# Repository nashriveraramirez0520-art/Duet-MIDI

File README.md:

# Duet-MIDI

I wanted to make something I could use to play both melodies and drums without needing two separate controllers. That is where Duet-MIDI started: eight touch pads, two modes, and a few extra controls to make it more fun to play.

This is my project for **Hack Club Half Life, Week 3: Music**. The schematic and PCB layout are finished, the Gerbers have been exported and checked, and the first enclosure version is modeled in Onshape. I have also prepared a first CircuitPython firmware version. I still need to print it, build the board, and test the firmware, so the pictures below are from KiCad, not a working prototype.

## What I want it to do

In melody mode, the eight pads will play notes from a scale, with buttons to move up or down an octave. In drum mode, the same pads will trigger different drum sounds. I added a mode button so I can switch between them instead of having to choose just one idea.

There is also a slider, a rotary encoder with a push switch, and a function button. Their exact MIDI assignments are still something I need to work out in the firmware. Eight RGB LEDs will give feedback for the mode and the pads being played.

It will connect to a computer over USB for both power and MIDI. The sound will come from a software instrument or drum sampler on the computer.

## The board

The PCB is **100 × 91.75 mm**, with two copper layers and four M2 mounting holes. I kept the touch pads in two rows of four, put the slider on the left, and placed the other controls below the pads. The RGB LEDs sit on the back and shine through eight openings near the top.

| Part | What it does |
| --- | --- |
| Waveshare ESP32-S3-Zero | USB connection and main controller |
| 8 capacitive touch pads | Note and drum inputs |
| MCP23008 | Reads the four buttons and the encoder push switch |
| Rotary encoder and 10 kΩ slider | Additional MIDI controls |
| 8 SK6812MINI-E RGB LEDs | Visual feedback |
| 74AHCT125 | Converts the RGB data signal from 3.3 V to 5 V |

## Getting the layout finished

Routing took a lot of small fixes. I had to work around the touch pads, connect the LEDs in the right order, and keep checking the remaining unconnected items as I went. Eventually the routing check reached zero violations and zero unconnected items with schematic parity turned off. That was a really nice point to reach after seeing the list slowly go down.

I then moved the reference text that was outside the board, added the control labels, and checked the exported copper, outline, and drill layers in Gerber Viewer.

[Routing check screenshot](docs/images/routing-drc.png) · [Back view](docs/images/pcb-back-3d.png)

The routing screenshot is from before the final text cleanup. Five DRC checks were disabled in that run; the details and the remaining manufacturing checks are in [pcb/README.md](pcb/README.md). The electrical behavior still needs to be tested on real hardware.

## The enclosure

I wanted a case I could open again, with the touch area accessible and a window underneath to show part of the PCB. V1 has a separate lid, four button extensions, a knob for the encoder, and a grip for the slider. The lid uses the same four M2 mounting positions as the board.

I had to lower the ESP32 mounting height to keep the case even across the top. I also adjusted the small control sockets and checked the slider at the center and both ends. The next step is a real fit test, starting with the small pieces before printing the whole enclosure.

[Enclosure files and assembly notes](cad/README.md) — includes individual STEP and STL parts plus a reference assembly. The bottom window is designed for separate 1 mm acrylic.

## Files

- [KiCad project](pcb/Duet-MIDI.kicad_pro), [schematic](pcb/Duet-MIDI.kicad_sch), and [PCB](pcb/Duet-MIDI.kicad_pcb).
- [Gerber ZIP](pcb/Duet-MIDI-Gerbers.zip) and [individual manufacturing files](pcb/gerbers/).
- [PCB notes and library setup](pcb/README.md).
- [CircuitPython firmware V1](firmware/), [enclosure V1](cad/), and [development journal](JOURNAL.md).
- [BOM draft](BOM.csv), with quantities extracted from the PCB. Exact parts, suppliers and prices are still pending; see [BOM notes](docs/BOM-notes.md).

To open the design, download the repository and open `pcb/Duet-MIDI.kicad_pro` in **KiCad 10**. The custom touch-pad footprint and the Hack Club libraries used by the design are included with project-relative paths.

## Firmware progress

The first CircuitPython version now includes both pad modes, octave buttons, a panic button, slider modulation, encoder volume with push-to-reset, and RGB feedback. Desktop tests cover the note and control logic, but I have not tested USB MIDI or any of the physical controls on the board yet. Touch thresholds, encoder settings, lighting and power use still need checking.

## What is next

The next steps are to finish the parts list, confirm the manufacturing limits, print and fit-test enclosure V1, and test the first firmware version on hardware. After assembly, I will need to test USB MIDI, calibrate the touch pads, and check the buttons, slider, encoder, and lighting together.

One thing still to confirm before ordering is the **0.20 mm copper clearance around the internal LED cutouts**. The LED brightness and USB power budget also need to be handled before running the assembled board.

## Editable CAD Source(Onshape)
https://cad.onshape.com/documents/5af46204eeb29ad0fa03019d/w/52b0aef6fb09ac80a2bff0bc/e/92c0bc1531caa20fbf243b4c?renderMode=0&uiState=6ade9d325837a28337909538

## References

I started from [Kai Pereira's MIDI Keypad guide](https://github.com/KaiPereira/MIDI-Keypad) and developed this layout around the two-mode idea and the extra controls. The Waveshare symbol and footprint come from [Hackclub KiCad Libraries](https://github.com/KaiPereira/Hackclub-KiCad-Libraries); see [the attribution notes](pcb/libraries/README.md).

Project by **Nash Andrés Rivera Ramírez**.

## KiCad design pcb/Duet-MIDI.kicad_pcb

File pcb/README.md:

# PCB files

The schematic, routed PCB, project rules, custom libraries, and manufacturing exports are here. Open `Duet-MIDI.kicad_pro` in KiCad 10 with the folder structure intact.

## Libraries

`Duet.pretty` contains the eight-pad touch footprint. The project-local `fp-lib-table` also registers `libraries/Hackclub.pretty` under its original name, **Hackclub Footprints**. `sym-lib-table` registers the supplied **Hackclub Symbols** library. Standard components use KiCad's installed libraries.

The Waveshare 3D model is optional and is not bundled here. To display it, download the upstream Hackclub KiCad Libraries and set `HACKCLUB_3DMODEL_DIR` to its `3D models` folder. Missing 3D models do not remove the component footprints from the PCB.

## Board and exports

- Board outline: 100 × 91.75 mm; two copper layers; nominal thickness 1.6 mm.
- Four 2.2 mm non-plated mounting holes for M2 hardware.
- Eight routed openings for the reverse-mount LEDs.
- Seven Gerber layers, separate plated/non-plated drill files, and a Gerber job file are in `gerbers/`.
- `Duet-MIDI-Gerbers.zip` contains the manufacturing export reviewed in Gerber Viewer.

The PCB, schematic, project, and custom rule files are the uploaded design files, unchanged. Only the library registration tables were adjusted for portability. The exports are from the earlier fabrication export in the same design session; regenerate them after any further board edits.

## Checks and remaining work

The supplied routing screenshot shows zero DRC violations and zero unconnected items, with schematic parity disabled. Five checks were ignored: missing courtyard, track endpoint not centered on via, tuning profile track geometries, footprint filter mismatch, and component type versus footprint-pad mismatch. A later parity check identified four PCB-only mounting footprints.

The older `.rpt` files in the uploaded archive predate the final routing fixes and are not included as a final passing report. Generate a fresh report from this project before placing an order.

The global copper-to-edge minimum is 0.50 mm. The custom rule in `Duet-MIDI.kicad_dru` allows 0.20 mm around LED footprint cutouts; the chosen manufacturer must accept that clearance. Exact purchased LED, slider, encoder, and switch variants still need to be matched to their footprints. Use an AHCT125 variant with the intended input thresholds rather than substituting an HC/AHC part without checking compatibility.

Hardware operation has not been tested. Touch calibration, MIDI behavior, RGB brightness/current limits, and the USB power budget remain part of firmware and prototype validation. Some 3D models are absent in the screenshots.

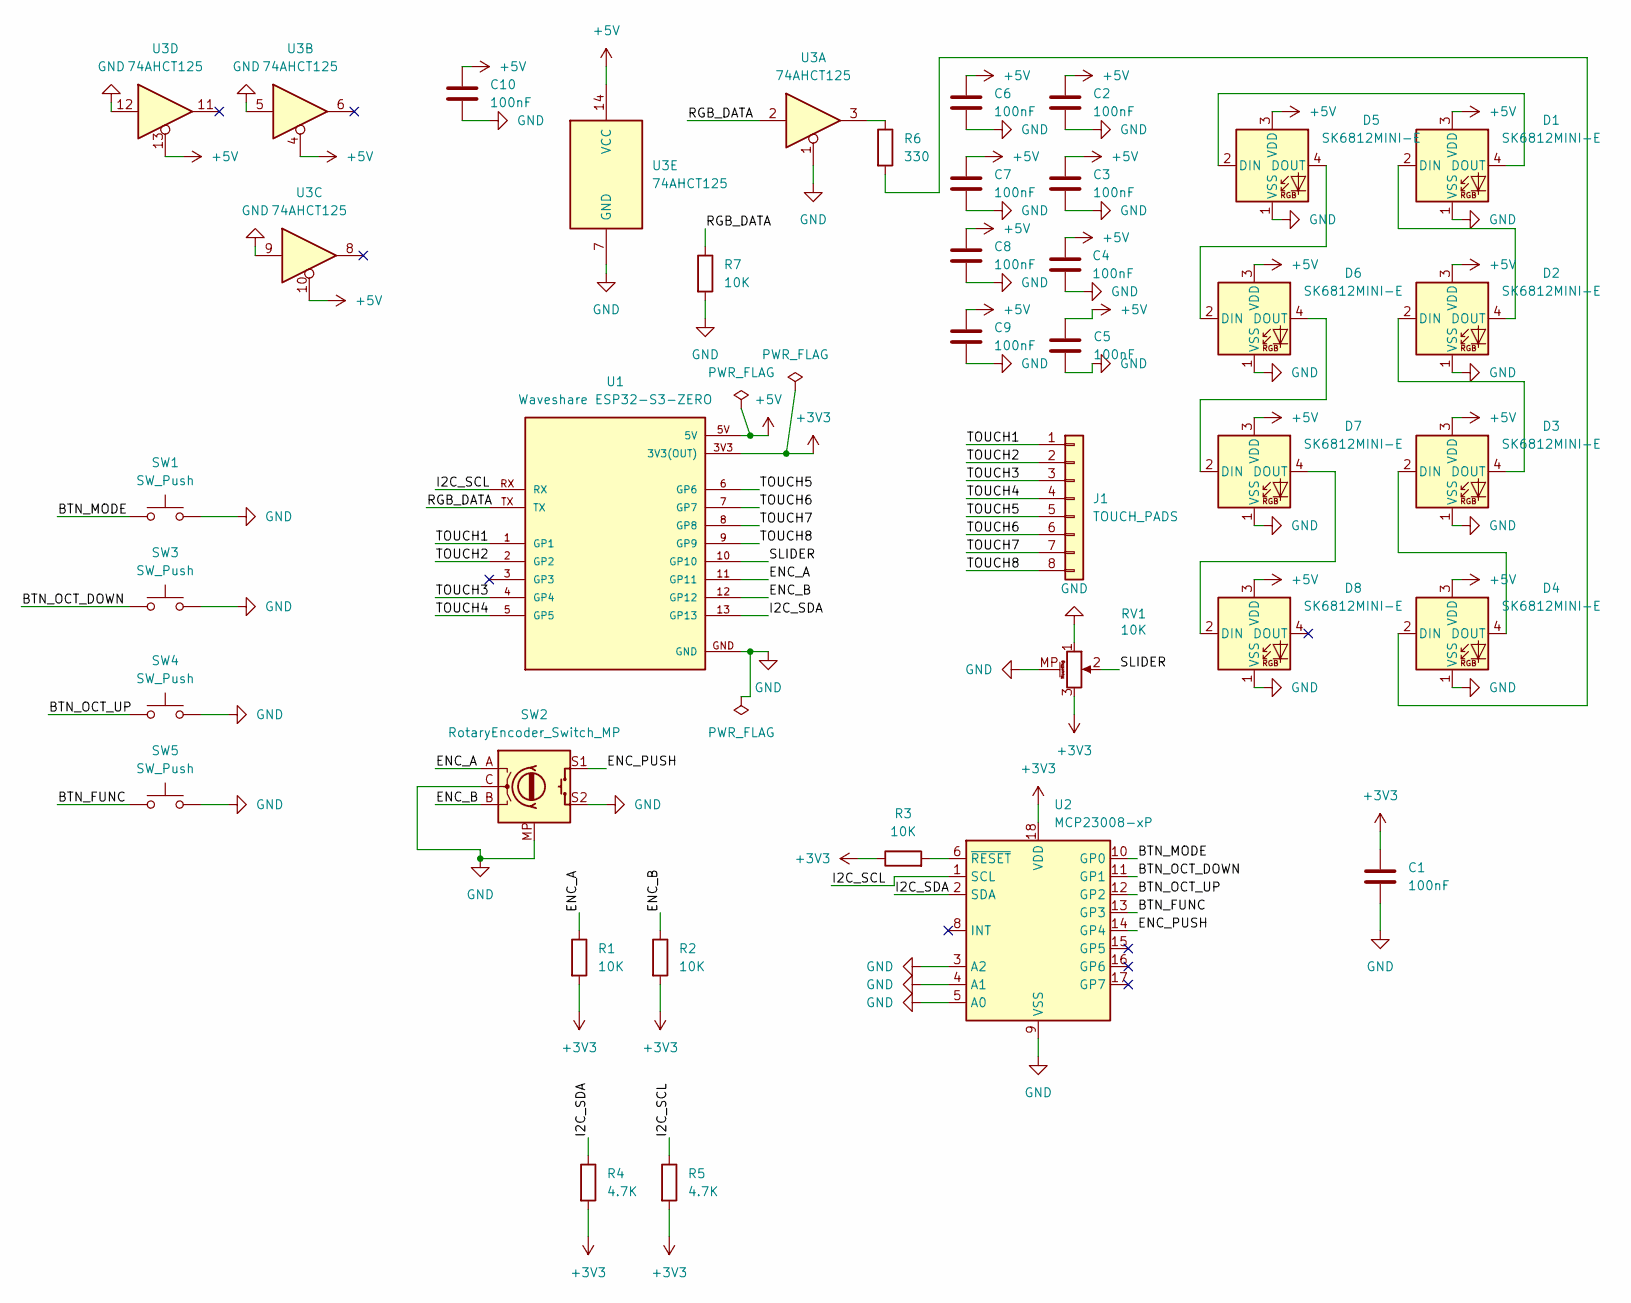
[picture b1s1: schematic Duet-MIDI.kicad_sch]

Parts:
C1, C2, C3, C4, C5, C6, C7, C8, C9, C10: 100nF; C_0805_2012Metric_Pad1.18x1.45mm_HandSolder
D1, D2, D3, D4, D5, D6, D7, D8: SK6812MINI-E; LED_SK6812MINI-E_3.2x2.8mm_P1.5mm_ReverseMount
J1: TOUCH_PADS; Duet_TouchPads_8
R1, R2, R3, R7: 10K; R_0805_2012Metric_Pad1.20x1.40mm_HandSolder
R4, R5: 4.7K; R_0805_2012Metric_Pad1.20x1.40mm_HandSolder
R6: 330; R_0805_2012Metric_Pad1.20x1.40mm_HandSolder
RV1: 10K; Potentiometer_Bourns_PTA3043_Single_Slide
SW1, SW3, SW4, SW5: SW_Push; SW_PUSH_6mm_H4.3mm
SW2: RotaryEncoder_Switch_MP; RotaryEncoder_Alps_EC11E-Switch_Vertical_H20mm
U1: Waveshare ESP32-S3-ZERO; Waveshare ESP32-S3-Zero; PARTREV NA
U2: MCP23008-xP; DIP-18_W7.62mm
U3: 74AHCT125; SOIC-14_3.9x8.7mm_P1.27mm

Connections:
+3V3: C1.1, R1.2, R2.2, R3.1, R4.2, R5.2, RV1.3, U1.3V3 (3V3(OUT)), U2.18 (VDD)
+5V: C2.1, C3.1, C4.1, C5.1, C6.1, C7.1, C8.1, C9.1, C10.1, D1.3 (VDD), D2.3 (VDD), D3.3 (VDD), D4.3 (VDD), D5.3 (VDD), D6.3 (VDD), D7.3 (VDD), D8.3 (VDD), U1.5V, U3.4, U3.10, U3.13, U3.14 (VCC)
/BTN_FUNC: SW5.1, U2.13 (GP3)
/BTN_MODE: SW1.1, U2.10 (GP0)
/BTN_OCT_DOWN: SW3.1, U2.11 (GP1)
/BTN_OCT_UP: SW4.1, U2.12 (GP2)
/ENC_A: R1.1, SW2.A, U1.11 (GP11)
/ENC_B: R2.1, SW2.B, U1.12 (GP12)
/ENC_PUSH: SW2.S1, U2.14 (GP4)
/I2C_SCL: R5.1, U1.RX, U2.1 (SCL)
/I2C_SDA: R4.1, U1.13 (GP13), U2.2 (SDA)
/RGB_DATA: R7.1, U1.TX, U3.2
/SLIDER: RV1.2, U1.10 (GP10)
/TOUCH1: J1.1, U1.1 (GP1)
/TOUCH2: J1.2, U1.2 (GP2)
/TOUCH3: J1.3, U1.4 (GP4)
/TOUCH4: J1.4, U1.5 (GP5)
/TOUCH5: J1.5, U1.6 (GP6)
/TOUCH6: J1.6, U1.7 (GP7)
/TOUCH7: J1.7, U1.8 (GP8)
/TOUCH8: J1.8, U1.9 (GP9)
GND: C1.2, C2.2, C3.2, C4.2, C5.2, C6.2, C7.2, C8.2, C9.2, C10.2, D1.1 (VSS), D2.1 (VSS), D3.1 (VSS), D4.1 (VSS), D5.1 (VSS), D6.1 (VSS), D7.1 (VSS), D8.1 (VSS), R7.2, RV1.1, RV1.MP (MountPin), SW1.2, SW2.C, SW2.MP, SW2.S2, SW3.2, SW4.2, SW5.2, U1.GND, U2.3 (A2), U2.4 (A1), U2.5 (A0), U2.9 (VSS), U3.1, U3.5, U3.7 (GND), U3.9, U3.12
unnamed: D1.2 (DIN), D2.4 (DOUT)
unnamed: D1.4 (DOUT), D5.2 (DIN)
unnamed: D2.2 (DIN), D3.4 (DOUT)
unnamed: D3.2 (DIN), D4.4 (DOUT)
unnamed: D4.2 (DIN), R6.2
unnamed: D5.4 (DOUT), D6.2 (DIN)
unnamed: D6.4 (DOUT), D7.2 (DIN)
unnamed: D7.4 (DOUT), D8.2 (DIN)
unnamed: R6.1, U3.3
unnamed: R3.2, U2.6 (~RESET)

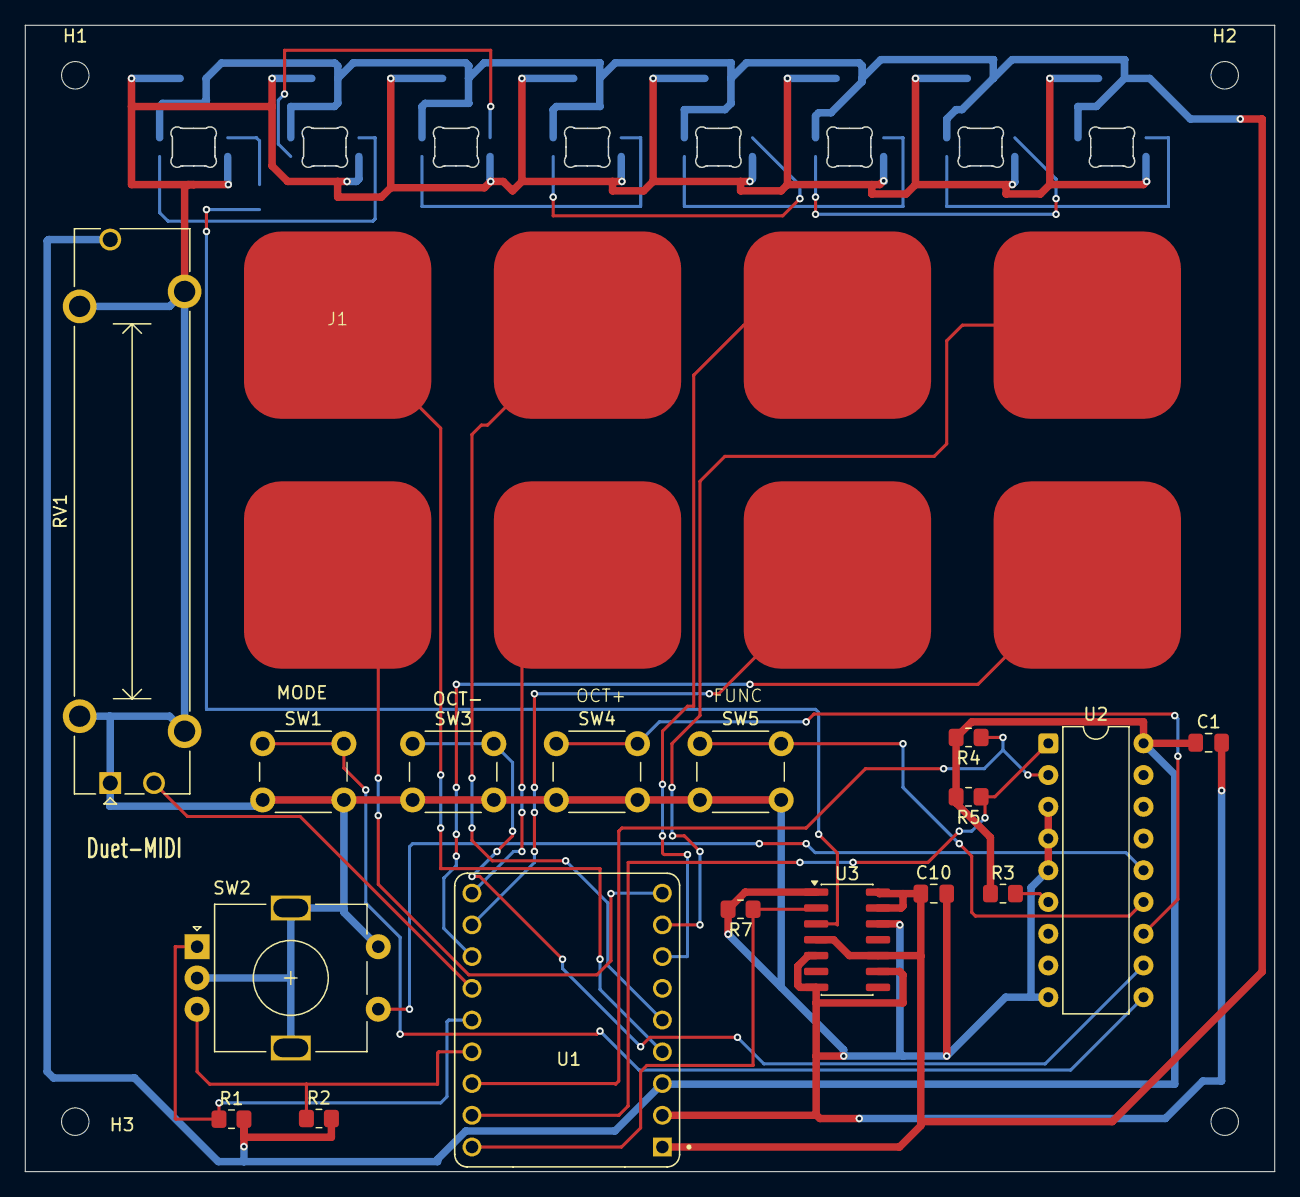
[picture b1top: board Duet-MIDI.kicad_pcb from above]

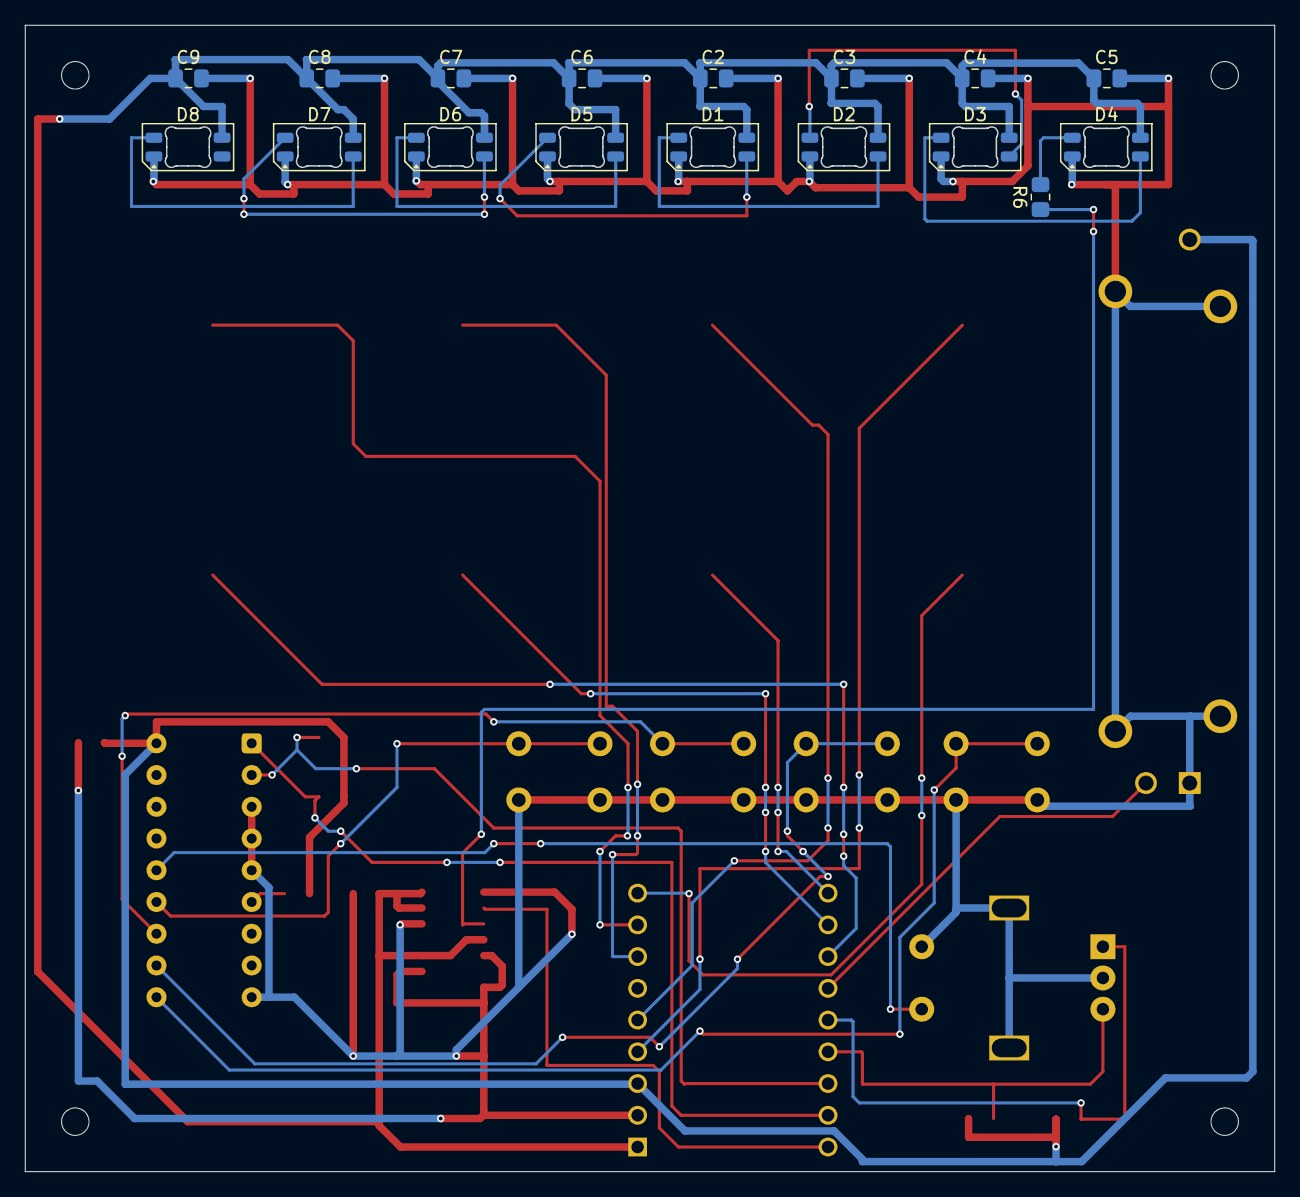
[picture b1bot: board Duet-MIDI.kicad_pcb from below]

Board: 2 copper layers, 100.0 x 91.8 mm, 39 parts (17 on the bottom side), 32 nets.

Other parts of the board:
H1, H2, H3: MountingHole_2.2mm_M2
REFH4: MountingHole_2.2mm_M2

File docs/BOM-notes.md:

# BOM draft: quantities extracted, sourcing still pending

`BOM.csv` now contains the components required for one assembled Duet-MIDI, plus its enclosure and connection hardware. Prices, suppliers and purchase links are blank where no exact part/order has been selected. This is **not a priced, submission-ready BOM**. Do not treat blank amounts as zero.

The inventory was extracted from the routed PCB, rather than estimated from the reference tutorial:

| References | Quantity | Requirement |
| --- | ---: | --- |
| U1 | 1 | Waveshare ESP32-S3-Zero; fixed male-header mounting |
| U2 | 1 | MCP23008, DIP-18, 7.62 mm row spacing |
| U3 | 1 | 74AHCT125, SOIC-14 narrow 3.9 mm body, 1.27 mm pitch |
| D1-D8 | 8 | SK6812MINI-E RGB, reverse mount, 3.2 x 2.8 mm |
| SW1, SW3-SW5 | 4 | 6 x 6 mm through-hole pushbuttons, 4.3 mm model height |
| SW2 | 1 | Switched vertical EC11-type encoder matching the Alps EC11E-Switch footprint |
| RV1 | 1 | 10 kOhm linear Bourns PTA3043-compatible slide pot, 30 mm travel |
| C1-C10 | 10 | 100 nF ceramic, 0805; choose voltage rating suitable for 5 V rails |
| R1, R2, R3, R7 | 4 | 10 kOhm, 0805 |
| R4, R5 | 2 | 4.7 kOhm, 0805 |
| R6 | 1 | 330 Ohm, 0805 |

The eight touch pads (J1) are copper features on the PCB, not eight purchased sensors or a pin header. H1-H4 are mounting holes, not purchased electrical components. The PCB file labels the fourth hole `REFH4`; it still represents the fourth M2 mounting position.

## Decisions before purchasing

- **Encoder:** the imported generic 3D model has a slight mounting-pin mismatch with the assigned footprint. Select an exact part using its datasheet and compare pin spacing, body, shaft D-flat, thread and push travel. The knob is not proof that every EC11 part fits.
- **Slider:** confirm the complete orderable part number, pin locations, travel, resistance/taper and actuator dimensions. Do not order solely from the label "10K". Its 3D transform was corrected locally after the originally uploaded KiCad sources; preserve the user's latest KiCad file.
- **Pushbuttons:** the enclosure extensions assume the 4.3 mm-height model. A taller button changes the fit.
- **Headers:** two 1x9 strips, 2.54 mm pitch, male only. The user has a header kit; no extra purchase is budgeted for those strips. Confirm actual mounting height.
- **Screws/nuts:** four M2 through screws and four nuts. Screw length, head dimensions and any required washers still need selection against the actual stack. Mounting positions are shared by the PCB, case and lid.
- **PCB:** CSV quantity is one assembled board. Use the fabrication supplier's actual minimum order quantity and shipping when pricing; do not calculate an order for one if the supplier requires five.
- **Printing:** eight pieces total: bottom, lid, four buttons, knob and slider cap. Printing charges depend on the actual service/material, supports and revised lid geometry; obtain the real quote.
- **Acrylic:** separate 1 mm bottom window, nominal 85.6 x 65.6 mm with R3.8 corners. Include cutting/adhesive costs if they are not already available.
- **LED update:** LED apertures and downward hollow tubes were added in Onshape after the repository's enclosure V1 export. Obtain the revised Top Cover STEP before final manufacturing exports. Transparent light-pipe inserts remain optional/unselected and are not counted as already purchased.
- **USB:** one data-capable cable with USB-C at the board end; choose the other end to suit the computer.

For budget submission, include actual pack quantities, shipping, taxes if required by the program, and links to the exact variants. Spare components can be bought in larger packs, but label pack pricing separately from per-board quantities.

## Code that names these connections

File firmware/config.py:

"""Duet-MIDI PCB wiring and initial, uncalibrated hardware settings."""
import board

TOUCH_PINS = (board.IO1, board.IO2, board.IO4, board.IO5,
              board.IO6, board.IO7, board.IO8, board.IO9)
SLIDER_PIN = board.IO10
ENCODER_A_PIN = board.IO11
ENCODER_B_PIN = board.IO12
I2C_SDA_PIN = board.IO13
I2C_SCL_PIN = board.IO44
MCP23008_ADDRESS = 0x20
BUTTON_MODE = 0
BUTTON_OCTAVE_DOWN = 1
BUTTON_OCTAVE_UP = 2
BUTTON_FUNCTION = 3
BUTTON_ENCODER = 4

LED_PIN = board.IO43  # External chain, not board.NEOPIXEL (GPIO21).
LED_COUNT = 8
# Pad 1..8 -> chain positions 0..7. Confirm the desired association on hardware.
# Electrical chain: D4 -> D3 -> D2 -> D1 -> D5 -> D6 -> D7 -> D8.
PAD_LED_INDICES = (0, 1, 2, 3, 4, 5, 6, 7)
LED_BRIGHTNESS = 0.08
LED_PIXEL_ORDER = "GRB"  # Verify with a red/green/blue test.
LED_UPDATE_INTERVAL = 0.033

MELODY_NOTES = (60, 62, 64, 65, 67, 69, 71, 72)
DRUM_NOTES = (36, 38, 42, 46, 41, 43, 49, 51)
MELODY_CHANNEL = 0  # MIDI channel 1, zero based.
DRUM_CHANNEL = 9    # MIDI channel 10, zero based.
NOTE_VELOCITY = 100
MIN_OCTAVE_SHIFT = -2
MAX_OCTAVE_SHIFT = 2

CALIBRATION_SAMPLES = 40
CALIBRATION_INTERVAL = 0.025
TOUCH_PRESS_RATIO = 1.20
TOUCH_RELEASE_RATIO = 1.10
TOUCH_DEBOUNCE_SECONDS = 0.020
BUTTON_DEBOUNCE_SECONDS = 0.030

SLIDER_CC = 1  # Modulation; software instrument must listen to this CC.
SLIDER_ADC_MIN = 0
SLIDER_ADC_MAX = 65535
SLIDER_INVERT = False
SLIDER_FILTER_ALPHA = 0.20
SLIDER_CC_STEP = 2
CONTROL_UPDATE_INTERVAL = 0.020

ENCODER_CC = 7  # Channel volume; host mapping may need configuration.
ENCODER_INITIAL_VALUE = 64
ENCODER_DIRECTION = 1  # Change to -1 if clockwise decreases.
ENCODER_DIVISOR = 4    # Confirm counts per detent on the purchased encoder.
